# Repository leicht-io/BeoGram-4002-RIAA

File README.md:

# BeoGram 4002 RIAA Preamp

An open-source RIAA phono preamplifier board for the Bang & Olufsen **BeoGram 4002 / 4004** turntable, designed in KiCad.

| | |
|---|---|
| **Status** | Prototype v3 (SMD) – designed, not built yet. v2 was manufactured and tested working. |
| **Tool** | KiCad 10 |
| **Board** | 2-layer, 1.6 mm, ~112 × 202 mm |
| **Hardware licence** | [CERN-OHL-S v2](./LICENSE) |
| **Docs licence** | [CC BY-SA 4.0](./LICENSE-DOCS) |

> This project is community driven. Build reports, measurements and design improvements are very welcome – see [CONTRIBUTING.md](./CONTRIBUTING.md).
> Questions and build help: [Discussions](https://github.com/leicht-io/BeoGram-4002-RIAA/discussions).

---

## Contents

- [Technical overview](#technical-overview)
- [Connectors](#connectors)
- [Getting the fabrication files](#getting-the-fabrication-files)
- [Building one](#building-one)
- [Known issues and roadmap](#known-issues-and-roadmap)
- [Repository layout](#repository-layout)
- [Contributing](#contributing)
- [Safety and disclaimer](#safety-and-disclaimer)
- [License](#license)

---

## Technical overview

A dual-stage active/passive RIAA equalizer per channel, based on the classic LM833 application topology but using the **OPA2134** for lower distortion. Full details are in [docs/design-notes.md](./docs/design-notes.md).

- **Stage 1 (U5A / U6A):** non-inverting gain stage that sets the 3180 µs / 318 µs part of the RIAA curve.
- **75 µs network:** passive RC between the stages.
- **Stage 2 (U5B / U6B):** flat gain of about 4.75×.
- **Output:** 100 Ω (R113 / R213) in series with each output keeps cable capacitance away from the op-amp, and limits the current when the mute relay shorts the output.
- **Gain:** about 38 dB at 1 kHz (simulated, not yet measured). B&O's MMC cartridges give about 2.5–3 mV, so the output is roughly 200–250 mV.
- **Power:** an LM317 makes about 20.8 V from the turntable's 30 V rail, which is unregulated (B&O bridge rectifier and 4000 µF). The op-amps run from this single supply.
- **Bias:** each channel has a filtered half-supply reference (`VREF_L` / `VREF_R`). Stage 1 is biased from it, so supply ripple is not amplified, and stage 2 is DC-coupled to stage 1. R103/R203 (47 k) also set the 47 kΩ cartridge load.
- **Grounding:** each pickup return runs next to its signal trace and joins GND at one point, at the input stage (net ties NT1/NT2).
- **Mute relay:** an Omron G6K-2F-Y (24 V DC coil) shorts both outputs to ground until the turntable's `RELAY ON` signal has been present for a while. The delay is set with RV1, and the board mutes instantly when the signal drops. Q1 is a Darlington (BCV49), as on the original B&O board.
- **Capacitors:** ceramic wherever a ceramic works. Six electrolytics remain (C103/C203, C106/C206, C108/C208), where a ceramic would pick up vibration or add distortion (see the [design notes](./docs/design-notes.md#capacitors)).

### Simulated response

Simulated with nominal part values, an ideal source and a 47 kΩ amplifier input. It has not been measured yet.

| Frequency | v3 deviation from RIAA | v2 deviation from RIAA |
|---|---|---|
| 20 Hz | −0.63 dB | −0.85 dB |
| 50 Hz | −0.08 dB | −0.23 dB |
| 100 Hz | +0.03 dB | −0.12 dB |
| 1 kHz | 0 (reference) | 0 (reference) |
| 10 kHz | −0.02 dB | +0.70 dB |
| 20 kHz | −0.03 dB | +0.73 dB |

The roll-off below 50 Hz comes from the coupling capacitors. Real boards also vary with the 5 % tolerance of the RIAA film capacitors. To regenerate the chart after changing values, edit them in `scripts/riaa_response.py` and run `python3 scripts/riaa_response.py images/riaa-response.svg`.

## Connectors

The board takes the place of B&O's PCB 8, the muting module (8005014 in the 4002, 8005022 with remote control in the 4004). Pin *n* of the original 9-pin P8 and P10 is pins 2*n*−1 and 2*n* here.

**P8 – From main PCB** (2×9, 2.54 mm)

| Pin | Signal |
|---|---|
| 1, 2 | RELAY ON |
| 3, 4 | GND (main board) |
| 5, 6 | Pickup cable shields (GND) |
| 7, 8 | L IN (pickup) |
| 9, 10 | L pickup return (joins GND only at NT1) |
| 11, 12 | R IN (pickup) |
| 13, 14 | R pickup return (joins GND only at NT2) |
| 15, 16 | 21 V (relay supply) |
| 17, 18 | 30 V (preamp supply) |

**P10 – From Keyboard** (2×9, 2.54 mm). Power only; the other pins are not connected. Like the original module, the board passes 30 V, 21 V and GND from P8 through to the keyboard.

| Pin | Signal |
|---|---|
| 3, 4 | 30 V |
| 11, 12 | 21 V |
| 13, 14 | GND |

**P9 – Output** (1×6, 2.54 mm). Same pin layout as the original P9, so the turntable's own output harness fits.

| Pin | Signal |
|---|---|
| 1 | L OUT (DIN pin 3) |
| 3 | R OUT (DIN pin 5) |
| 5 | GND, signal ground (DIN pin 2) |
| 6 | GND, chassis |
| 2, 4 | Not connected (Beomaster 2400 remote lines on a 4004, see below) |

**BeoGram 4004:** the 4004's PCB 8 (8005022) also holds the remote-control circuit for a Beomaster 2400 (start, pause and stop from the PHONO and STAND BY keys). This board doesn't have it:

- P10 carries the same 30 V, 21 V and GND as on the 4004 board, so the turntable's own keys work. The remote-control pins of P10 are left open, so the Beomaster 2400 remote can't start, pause or stop the turntable.
- The 4004's P9 harness has two extra wires on pins 2 and 4 (DIN pins 6 and 7, the Beomaster's remote signals). Those pins aren't connected on this board, so the harness can be plugged in as it is.

## Getting the fabrication files

Gerbers and other fabrication files are **not committed** to the repository. CI generates them from the KiCad sources on every push, so they always match the design:

- **Releases:** every tagged version (`v*`) has a [GitHub release](https://github.com/leicht-io/BeoGram-4002-RIAA/releases) with the gerber zip, a schematic PDF, the BOMs, the pick-and-place files and renders.
- **Latest `main` / any PR:** open the latest [KiCad workflow run](https://github.com/leicht-io/BeoGram-4002-RIAA/actions/workflows/kicad.yml) and download the `fabrication` artifact (you must be logged in to GitHub).
- **Locally:** in KiCad, *File → Fabrication Outputs*, or run the `kicad-cli` commands from [`.github/workflows/kicad.yml`](./.github/workflows/kicad.yml).

The gerbers of the first (v1) prototype are no longer in the tree but remain in the git history.

The CI produces these BOMs and pick-and-place (CPL) files:

| File | Contents |
|---|---|
| `RIAA-bom-full.csv` | Every part, with manufacturer, manufacturer part number (MPN) and LCSC number. The `Assembly` column says whether a part is assembled by JLCPCB or soldered by hand. |
| `RIAA-bom-jlcpcb.csv` + `RIAA-cpl-jlcpcb.csv` | Upload-ready files for JLCPCB SMT assembly (parts from LCSC; film capacitors excluded). |
| `RIAA-bom-pcbway.csv` + `RIAA-cpl-pcbway.csv` | Upload-ready files for PCBWay turnkey assembly. The BOM lists every part, including the film capacitors and connectors, by manufacturer and MPN, with the LCSC number as distributor part number. The CPL lists the surface-mount parts. |

Every part in the schematic has `Manufacturer` and `MPN` fields; parts JLCPCB can place also have an `LCSC PN` field.

## Building one

1. Order the board with assembly from one of the two fabs:
   - **JLCPCB:** SMT assembly with the gerber zip, `RIAA-bom-jlcpcb.csv` and `RIAA-cpl-jlcpcb.csv`. The film capacitors are not included (step 2).
   - **PCBWay:** turnkey assembly with the gerber zip, `RIAA-bom-pcbway.csv` and `RIAA-cpl-pcbway.csv`. PCBWay sources every part, including the through-hole film capacitors and connectors, so step 2 is not needed.

   Check the part rotations and the polarity of the diodes and electrolytic capacitors in the fab's preview before confirming. Stock of the 0.1 % resistors in the RIAA network is low at times. A 1 % part of the same value is fine if one runs out.
2. For a JLCPCB board, hand-solder the parts marked `Hand` in `RIAA-bom-full.csv`: the film capacitors C101, C102, C105 and C201, C202, C205. C102/C202 and C105/C205 set the RIAA time constants, so tight-tolerance or matched parts give the most accurate curve.
3. Set RV1 for the unmute delay you want (about 1 s to 10 s).
4. Install it in the turntable. *An illustrated installation guide is still missing – contributions are very welcome.*

Please post a **Build report** issue when you have built one, whether it worked or not.

## Known issues and roadmap

- [ ] **v3 has not been built yet.** The hum, bias and mute-relay fixes are simulated and the board passes DRC/ERC, but they still need to be confirmed on a real board (see [CHANGELOG.md](./CHANGELOG.md)).
- [ ] **Hum on some turntables (v2).** If a v3 board still hums, check the 30 V rail, P10, and whether the turntable joins the pickup returns to ground somewhere else (see the [design notes](./docs/design-notes.md#hum-and-ground-loops)).
- [ ] **No measurements yet:** RIAA deviation, noise and THD are still missing.
- [ ] **No installation guide or photos yet.**
- [ ] **No BeoGram 4004 remote control:** start, pause and stop from a Beomaster 2400 are not supported (see [Connectors](#connectors)).

## Repository layout

```
RIAA.kicad_pro / .kicad_sch / .kicad_pcb   KiCad project
parts/                                     Project-local footprints (OPA2134 D8)
3d-parts/                                  STL files for the 3D-printed board guides
docs/                                      Design notes
images/                                    Renders and photos
scripts/make_bom.py                        Builds the full, JLCPCB and PCBWay BOMs and CPL files (used by CI)
scripts/riaa_response.py                   Simulates the RIAA response and draws images/riaa-response.svg
.github/                                   CI workflow, issue and PR templates
```

## Contributing

See [CONTRIBUTING.md](./CONTRIBUTING.md). In short: open an issue or discussion first for design changes, keep each PR focused, and include screenshots of what you changed in the schematic or PCB.

## Safety and disclaimer

This board connects to the turntable's internal 30 V supply. Vintage equipment can be damaged by wiring mistakes. Everything here is provided **as is, without any warranty** (see the licence), and you build and install it at your own risk.

Bang & Olufsen, BeoGram and related names are trademarks of their owners. This project is not affiliated with or endorsed by Bang & Olufsen.

## License

- **Hardware design files** (KiCad, STL): [CERN Open Hardware Licence v2 – Strongly Reciprocal](./LICENSE) (CERN-OHL-S-2.0)
- **Documentation and images:** [Creative Commons Attribution-ShareAlike 4.0](./LICENSE-DOCS) (CC-BY-SA-4.0)
- **Scripts** (`scripts/`): GPL-3.0-or-later

## Author

Christian Leicht – [leicht.io](https://github.com/leicht-io)

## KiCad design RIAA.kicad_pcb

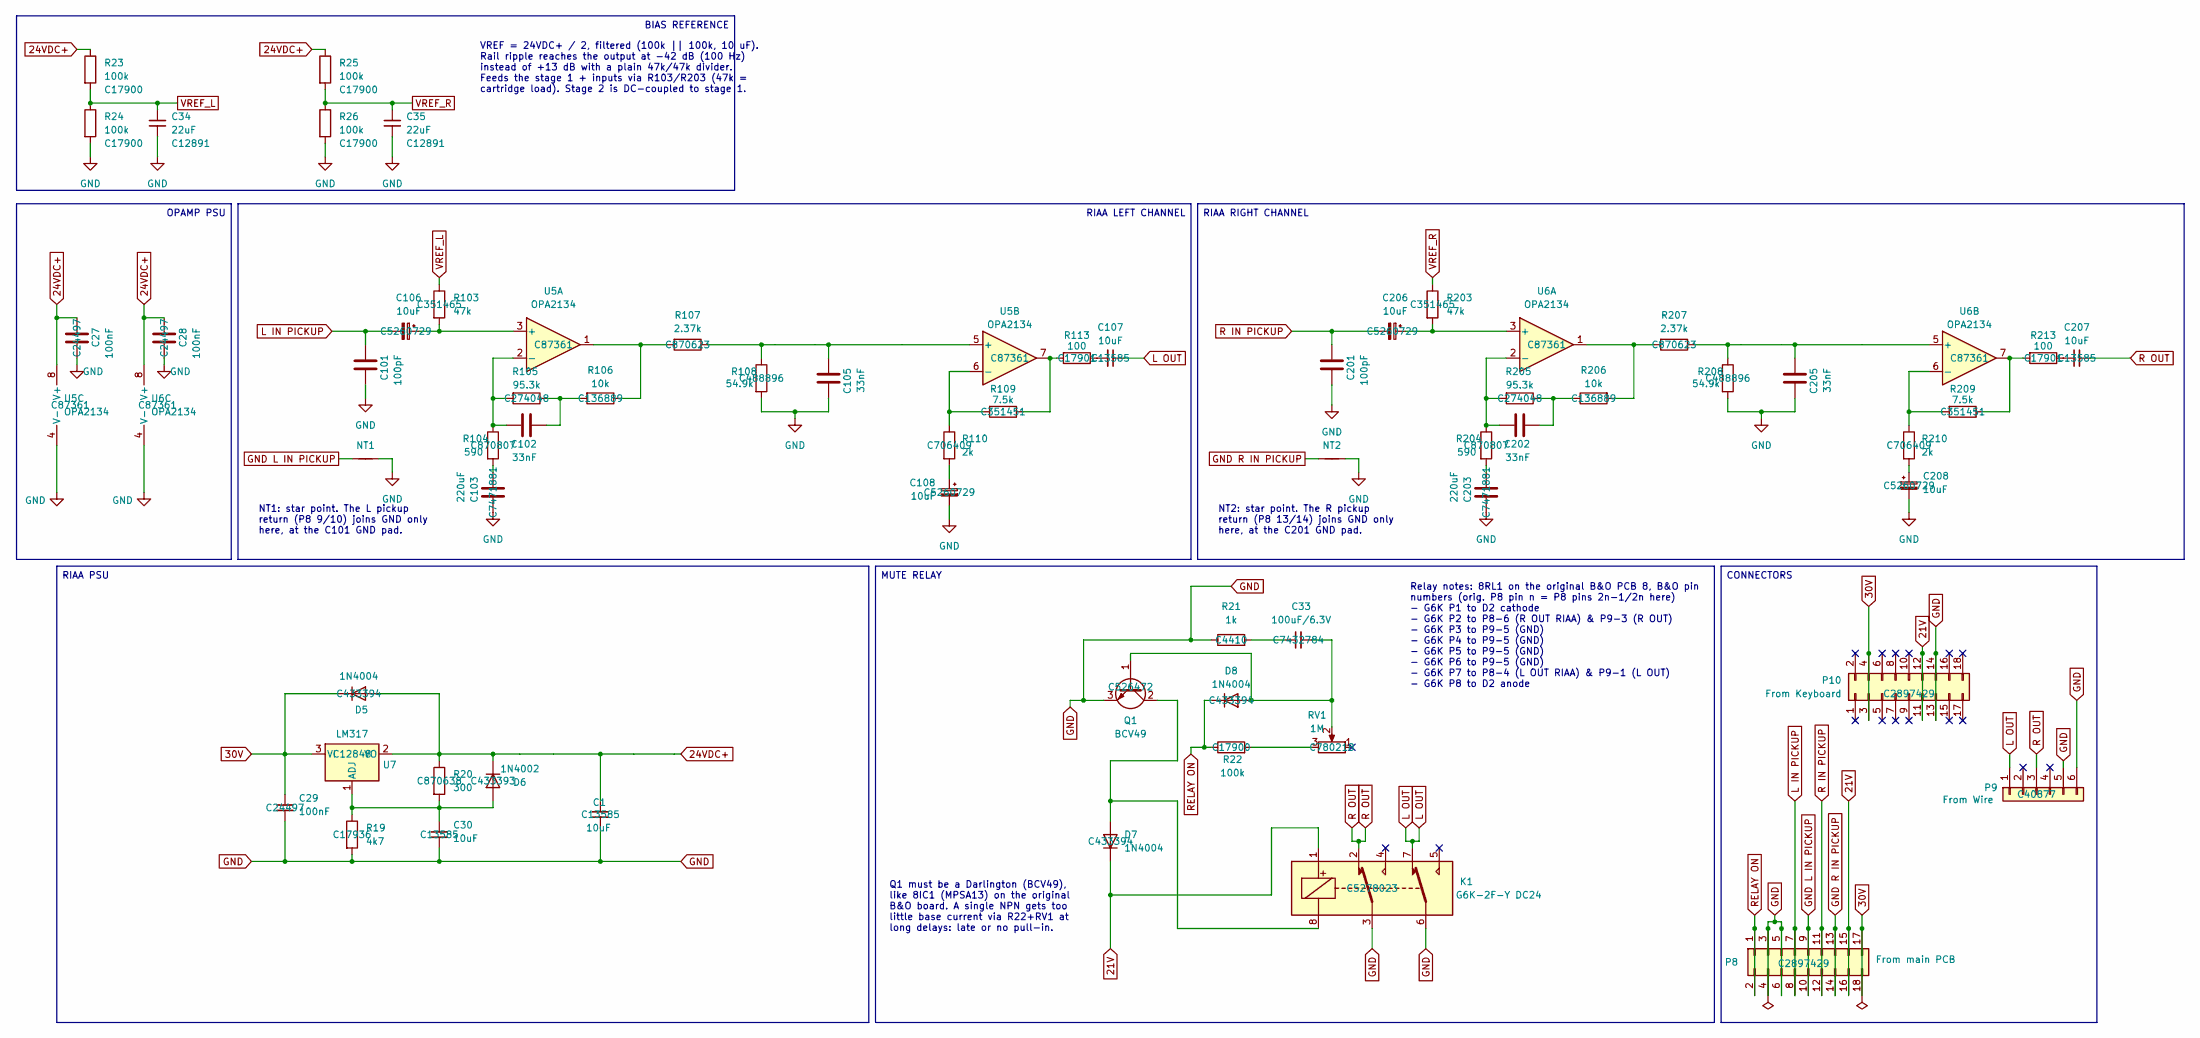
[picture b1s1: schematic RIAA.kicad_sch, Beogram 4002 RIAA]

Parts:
C1, C30, C107, C207: 10uF; C_1206_3216Metric_Pad1.33x1.80mm_HandSolder; MPN CL31A106KBHNNNE; LCSC PN C13585
C27, C28, C29: 100nF; C_1206_3216Metric_Pad1.33x1.80mm_HandSolder; MPN CL31B104KBCNNNC; LCSC PN C24497
C33: 100uF/6.3V; C_1206_3216Metric_Pad1.33x1.80mm_HandSolder; MPN HGC1206R5107M100NSPJ; LCSC PN C7432784
C34, C35: 22uF; C_1206_3216Metric_Pad1.33x1.80mm_HandSolder; MPN CL31A226KAHNNNE; LCSC PN C12891
C101, C201: 100pF; C_Rect_L7.2mm_W4.5mm_P5.00mm_FKS2_FKP2_MKS2_MKP2; MPN FKP2D001001D00JSSD
C102, C105, C202, C205: 33nF; C_Rect_L7.2mm_W4.5mm_P5.00mm_FKS2_FKP2_MKS2_MKP2; MPN MKS2C023301A00JSSD
C103, C203: 220uF; CP_Elec_6.3x7.7; MPN 189RV0019; LCSC PN C7471881
C106, C108, C206, C208: 10uF; CP_Elec_5x5.4; MPN FZ1V100M0506; LCSC PN C5260729
D5, D7, D8: 1N4004; D_SMA; MPN 1N4004G; LCSC PN C433394
D6: 1N4002; D_SMA; MPN 1N4002G; LCSC PN C433393
K1: G6K-2F-Y DC24; Relay_DPDT_Omron_G6K-2F-Y; MPN G6K-2F-Y-TR DC24; LCSC PN C5278023
NT1, NT2: NetTie_2; NetTie-2_SMD_Pad0.5mm
P8: From main PCB; PinSocket_2x09_P2.54mm_Horizontal; MPN PM254-2-09-W-8.5; LCSC PN C2897429
P9: From Wire; PinSocket_1x06_P2.54mm_Vertical; MPN 2.54-1*6P; LCSC PN C40877
P10: From Keyboard; PinSocket_2x09_P2.54mm_Horizontal; MPN PM254-2-09-W-8.5; LCSC PN C2897429
Q1: BCV49; SOT-89-3_Handsoldering; MPN BCV49TA; LCSC PN C526472
R19: 4k7; R_1206_3216Metric_Pad1.30x1.75mm_HandSolder; MPN 1206W4F4701T5E; LCSC PN C17936
R20: 300; R_1206_3216Metric_Pad1.30x1.75mm_HandSolder; MPN RT1206BRD07300RL; LCSC PN C870638
R21: 1k; R_1206_3216Metric_Pad1.30x1.75mm_HandSolder; MPN 1206W4F1001T5E; LCSC PN C4410
R22, R23, R24, R25, R26: 100k; R_1206_3216Metric_Pad1.30x1.75mm_HandSolder; MPN 1206W4F1003T5E; LCSC PN C17900
R103, R203: 47k; R_1206_3216Metric_Pad1.30x1.75mm_HandSolder; MPN PTFR1206B47K0P9; LCSC PN C351465
R104, R204: 590; R_1206_3216Metric_Pad1.30x1.75mm_HandSolder; MPN RT1206BRD07590RL; LCSC PN C870807
R105, R205: 95.3k; R_1206_3216Metric_Pad1.30x1.75mm_HandSolder; MPN RC1206FR-0795K3L; LCSC PN C274048
R106, R206: 10k; R_1206_3216Metric_Pad1.30x1.75mm_HandSolder; MPN RT1206BRD0710KL; LCSC PN C136889
R107, R207: 2.37k; R_1206_3216Metric_Pad1.30x1.75mm_HandSolder; MPN RT1206BRD072K37L; LCSC PN C870623
R108, R208: 54.9k; R_1206_3216Metric_Pad1.30x1.75mm_HandSolder; MPN RC1206FR-0754K9L; LCSC PN C488896
R109, R209: 7.5k; R_1206_3216Metric_Pad1.30x1.75mm_HandSolder; MPN PTFR1206B7K50P9; LCSC PN C351451
R110, R210: 2k; R_1206_3216Metric_Pad1.30x1.75mm_HandSolder; MPN RT1206BRD072KL; LCSC PN C706409
R113, R213: 100; R_1206_3216Metric_Pad1.30x1.75mm_HandSolder; MPN 1206W4F1000T5E; LCSC PN C17901
RV1: 1M; Potentiometer_Bourns_3314G_Vertical; MPN 3314G-1-105E; LCSC PN C780218
U5, U6: OPA2134; D8; MPN OPA2134UA/2K5; LCSC PN C87361
U7: LM317; TO-263-2; MPN LM317D2TR4G; LCSC PN C12848

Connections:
21V: D7.1 (K), K1.1, P8.15, P8.16, P10.11, P10.12
24VDC+: C1.1, C27.2, C28.2, D5.2 (A), D6.1 (K), R20.1, R23.1, R25.1, U5.8 (V+), U6.8 (V+), U7.2 (VO)
30V: C29.1, D5.1 (K), P8.17, P8.18, P10.3, P10.4, U7.3 (VI)
GND: C1.2, C27.1, C28.1, C29.2, C30.2, C34.2, C35.2, C101.1, C103.2, C105.1, C108.2, C201.1, C203.2, C205.1, C208.2, K1.3, K1.6, NT1.2, NT2.2, P8.3, P8.4, P8.5, P8.6, P9.5, P9.6, P10.13, P10.14, Q1.3 (E), R19.2, R21.1, R24.2, R26.2, R108.2, R208.2, U5.4 (V-), U6.4 (V-)
GND L IN PICKUP: NT1.1, P8.9, P8.10
GND R IN PICKUP: NT2.1, P8.13, P8.14
L IN PICKUP: C101.2, C106.2, P8.7, P8.8
L OUT: C107.2, K1.7, P9.1
unnamed: C33.2, R21.2
unnamed: C102.2, R105.1, R106.2
unnamed: C103.1, R104.2
unnamed: C107.1, R113.1
unnamed: C108.1, R110.2
unnamed: C202.2, R205.1, R206.1
unnamed: C203.1, R204.2
unnamed: C207.1, R213.1
unnamed: C208.1, R210.2
unnamed: C30.1, D6.2 (A), R19.1, R20.2, U7.1 (ADJ)
unnamed: D7.2 (A), K1.8, Q1.2 (C)
unnamed: C33.1, D8.2 (A), Q1.1 (B), RV1.2
unnamed: R22.2, RV1.3
unnamed: R106.1, R107.2, U5.1
unnamed: R109.1, R113.2, U5.7
unnamed: R206.2, R207.2, U6.1
unnamed: R209.1, R213.2, U6.7
unnamed: C106.1, R103.2, U5.3 (+)
unnamed: C102.1, R104.1, R105.2, U5.2 (-)
unnamed: C105.2, R107.1, R108.1, U5.5 (+)
unnamed: R109.2, R110.1, U5.6 (-)
unnamed: C206.1, R203.2, U6.3 (+)
unnamed: C202.1, R204.1, R205.2, U6.2 (-)
unnamed: C205.2, R207.1, R208.1, U6.5 (+)
unnamed: R209.2, R210.1, U6.6 (-)
R IN PICKUP: C201.2, C206.2, P8.11, P8.12
R OUT: C207.2, K1.2, P9.3
RELAY ON: D8.1 (K), P8.1, P8.2, R22.1
VREF_L: C34.1, R23.2, R24.1, R103.1
VREF_R: C35.1, R25.2, R26.1, R203.1

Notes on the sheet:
Relay notes: 8RL1 on the original B&O PCB 8, B&O pin numbers (orig. P8 pin n = P8 pins 2n-1/2n here) - G6K P1 to D2 cathode - G6K P2 to P8-6 (R OUT RIAA) & P9-3 (R OUT) - G6K P3 to P9-5 (GND) - G6K P4 to P9-5 (GND) - G6K P5 to P9-5 (GND) - G6K P6 to P9-5 (GND) - G6K P7 to P8-4 (L OUT RIAA) & P9-1 (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
RIAA RIGHT CHANNEL
RIAA LEFT CHANNEL
OPAMP PSU
CONNECTORS
RIAA PSU
MUTE RELAY
VREF = 24VDC+ / 2, filtered (100k || 100k, 10 uF). Rail ripple reaches the output at -42 dB (100 Hz) instead of +13 dB with a plain 47k/47k divider. Feeds the stage 1 + inputs via R103/R203 (47k = cartridge load). Stage 2 is DC-coupled to stage 1.
BIAS REFERENCE
NT1: star point. The L pickup return (P8 9/10) joins GND only here, at the C101 GND pad.
NT2: star point. The R pickup return (P8 13/14) joins GND only here, at the C201 GND pad.
Q1 must be a Darlington (BCV49), like 8IC1 (MPSA13) on the original B&O board. A single NPN gets too little base current via R22+RV1 at long delays: late or no pull-in.

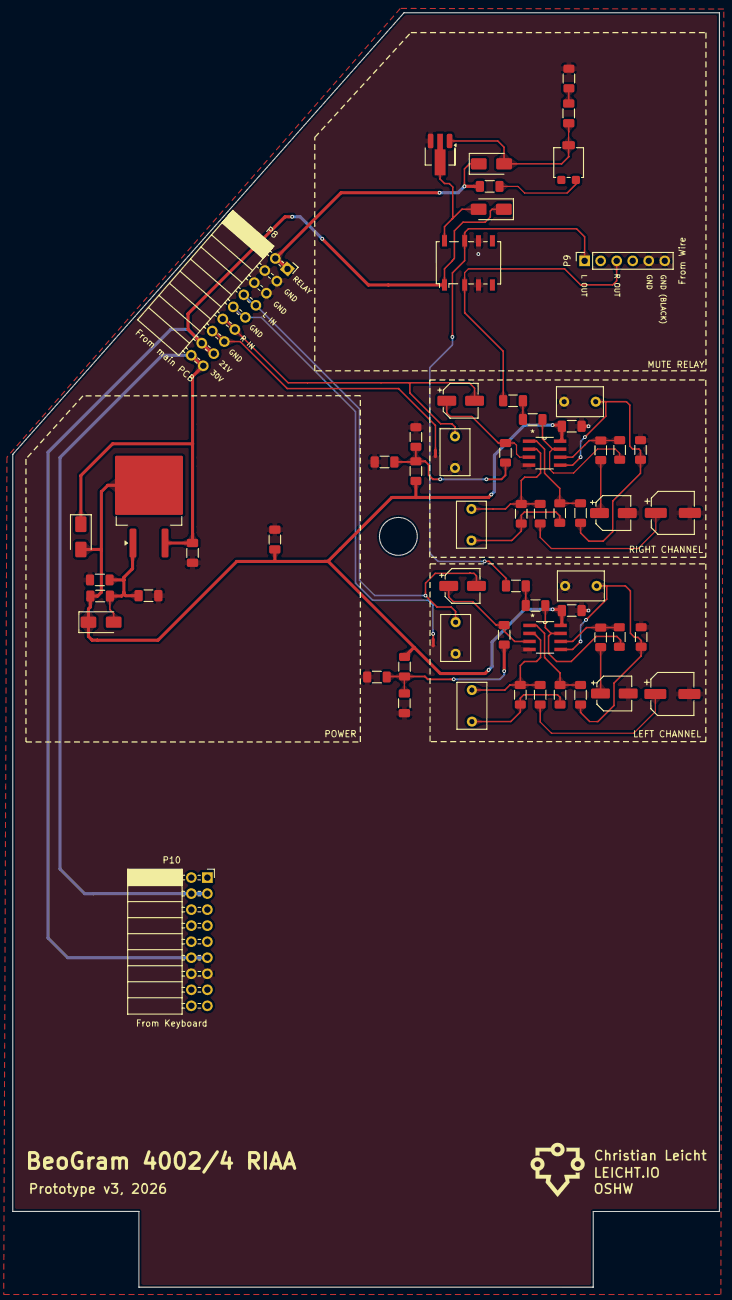
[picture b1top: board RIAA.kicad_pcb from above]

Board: 2 copper layers, 112.0 x 202.0 mm, 63 parts (0 on the bottom side), 38 nets.

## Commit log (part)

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2024-04-18 Create LICENSE
2024-04-18 feat: initial release.
2024-04-21 feat: updated docs.
2024-04-25 feat: updated schematics.
2025-01-01 Added 3d guidance parts
2025-01-01 feat: reversed D1.
2025-01-01 feat: Updated PSU resistor values.
2025-01-02 feat: Updated PCB.
2025-01-04 feat: Updated orientation of D1.
2025-01-04 feat: Updated image.
2025-01-05 feat:
2025-01-05 feat: added classic linear power supply
2025-01-06 WIP: Committing the changes from yesterday.
2025-01-06 WIP:
2025-01-06 WIP: Added gerber files.
2025-01-07 WIP: Started on 3v3 voltage regulator for esp32.
2026-01-26 WIP: Working on SMD version.
2026-01-27 WIP: Working on SMD.
2026-01-27 WIP: Added Bourne 3315J footprint.
2026-01-27 WIP: Finishing up SMD version.
2026-01-28 WIP: Adding LSCS PNs.
2026-02-16 Updated README.md and images.
2026-02-16 Removed image from README.md.
